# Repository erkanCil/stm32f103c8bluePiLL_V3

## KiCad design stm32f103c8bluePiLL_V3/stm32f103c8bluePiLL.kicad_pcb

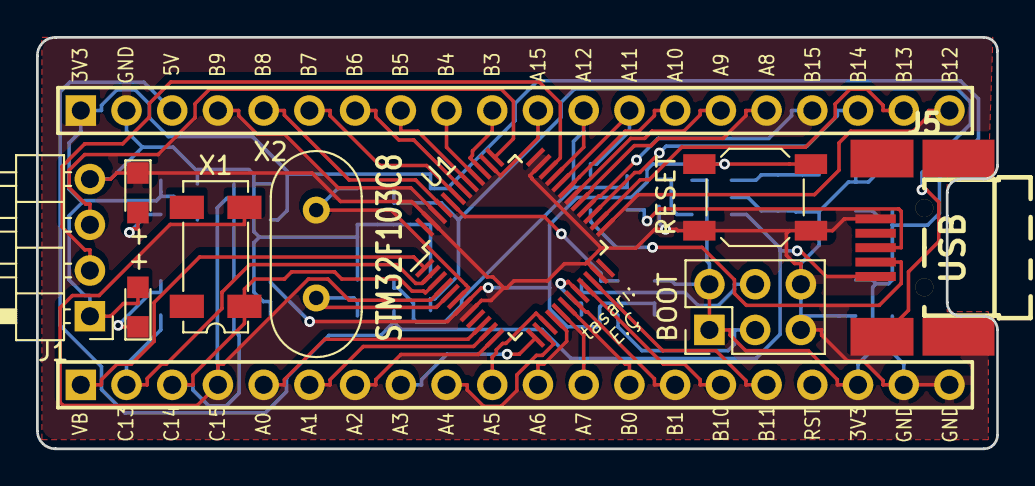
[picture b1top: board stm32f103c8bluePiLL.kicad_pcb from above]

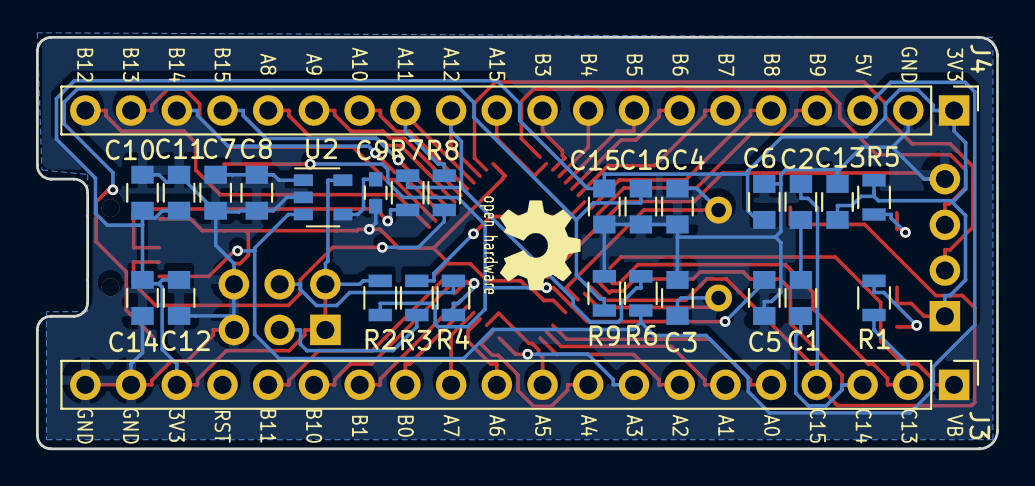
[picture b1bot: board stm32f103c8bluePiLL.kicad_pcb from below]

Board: 2 copper layers, 53.3 x 22.9 mm, 37 parts (28 on the bottom side), 53 nets.

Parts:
+: LED; LED_0805
+#2: GREEN; LED_0805
BOOT: HEADER_2X3; Pin_Header_Straight_2x03_Pitch2.54mm
C1, C2, C3, C4: 18pF; C_0805
C5: 100nF; C_0805
C6, C8, C11, C12, C13, C14, C15: 0.1uF; C_0805
C7: 1uF; C_0805
C9: 22nF; C_0603
C10: 10uF; C_0805
C16: 4.7nF; C_0805
J1: Conn_01x04; Pin_Header_Angled_1x04_Pitch2.54mm
J3, J4: Conn_01x20; Pin_Header_Straight_1x20_Pitch2.54mm
J5: USB_B_Mini; USB_Mini-B-NOSILK
R1, R5: 510; R_0805
R2: 1K; R_0805
R3, R4: 100K; R_0805
R6: 4K7; R_0805
R7, R8: 20R; R_0805
R9: 1M; R_0805
RESET: ReSet_Button; SW_SPST_SKQG
U1: STM32F103C8Tx; LQFP-48_7x7mm_Pitch0.5mm
U2: RT9193-33; SOT-23-5
X1: 32.768KHz; Crystal_SMD_SeikoEpson_MC306-4pin_8.0x3.2mm
X2: 8MHz; Crystal_HC49-4H_Vertical

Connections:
/5V: J4.3, J5.1, R6.1, U2.3
/BOOT0: BOOT.3, R3.2
/BOOT1: BOOT.4, R4.2
/D+: J5.3, R7.1
/D-: J5.2, R8.1
/PA0: J3.5, U1.10
/PA1: J3.6, U1.11
/PA2: J3.7, U1.12
/PA3: J3.8, U1.13
/PA4: J3.9, U1.14
/PA5: J3.10, U1.15
/PA6: J3.11, U1.16
/PA7: J3.12, U1.17
/PA8: J4.16, U1.29
/PA9: J4.15, U1.30
/PA10: J4.14, U1.31
/PA11: J4.13, R8.2, U1.32
/PA12: J4.12, R6.2, R7.2, U1.33
/PA15: J4.11, U1.38
/PB0: J3.13, U1.18
/PB1: J3.14, U1.19
/PB3: J4.10, U1.39
/PB4: J4.9, U1.40
/PB5: J4.8, U1.41
/PB6: J4.7, U1.42
/PB7: J4.6, U1.43
/PB8: J4.5, U1.45
/PB9: J4.4, U1.46
/PB10: J3.15, U1.21
/PB11: J3.16, U1.22
/PB12: J4.20, U1.25
/PB13: J4.19, U1.26
/PB14: J4.18, U1.27
/PB15: J4.17, U1.28
/PC13: J3.2, R1.1, U1.2
/PC14: C1.1, J3.3, U1.3, X1.1
/PC15: C2.1, J3.4, U1.4, X1.2
/RESET: C5.2, R2.2, RESET.1, U1.7
/SWCLK: J1.3, U1.37
/SWDIO: J1.2, U1.34
/VBAT: J3.1, U1.1
/VCC3V3: +.2, BOOT.1, BOOT.2, C6.1, C10.1, C11.1, C12.1, C13.1, C14.1, C15.1, J1.1, J3.18, J4.1, R2.1, R5.1, U2.5
GND: +#2.1, BOOT.5, BOOT.6, C3.2, C4.2, C5.1, C6.2, C7.2, C8.2, C9.2, C10.2, C11.2, C12.2, C13.2, C14.2, C15.2, C16.2, J1.4, J3.19, J3.20, J4.2, J5.5, R9.2, RESET.2, U1.8, U1.23, U1.35, U1.47, U2.2
unnamed: C1.2, C2.2
unnamed: C3.1, U1.5, X2.1
unnamed: C4.1, U1.6, X2.2
unnamed: C7.1, C8.1, U2.1
unnamed: C9.1, U2.4
unnamed: C16.1, J5.6, R9.1
unnamed: +.1, R1.2
unnamed: +#2.2, R5.2
unnamed: R3.1, U1.44
unnamed: R4.1, U1.20

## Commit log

2017-11-26 :lollipop: Added .gitattributes & .gitignore files
